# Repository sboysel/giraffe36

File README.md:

# giraffe36

A 36 key split keyboard with "long-necked" thumb clusters. Wired, powered by Raspberry Pi Picos, diodeless. Inspirations include Ferris Sweep / sweep36, draculad, samoklava, piantor.

**Status:** [v0.0.1](https://github.com/sboysel/giraffe36/releases/tag/v0.0.1) / [e54525c](https://github.com/sboysel/giraffe36/commit/e54525ce078f5a7b52e7f0cd5a91edfa0f02212c) prototypes have been tested and are functional. See [Tags](https://github.com/sboysel/giraffe36/tags).

## Goals

- simplicity
- declarative design ([ergogen](https://github.com/ergogen/ergogen) and specifically, [my fork](https://github.com/sboysel/ergogen))
- 5x3+3 wired split
- soldered MX to build plateless
- diodeless
- lowered thumb cluster comfortable to my hands
- to learn PCB design!

## Build

BOM

- 2x PCB (they are reversible, fabricated by JLCPCB)
- 2x Raspberry Pi Pico (I used [WeAct Studio Pi Picos](https://www.aliexpress.us/item/3256803521775546.html))
- 2x TRRS PJ-320A jack (4 pins)
- 36x MX switches

Be sure to use the `main` branch. Gerbers can be found in `output/pcbs/routed/`. Archives of the routed PCB and gerbers are located in `output/pcbs/routed/backups`. Firmware ([KMK](http://kmkfw.io/)) can be found in `firmware/kmk/`.

## Development 

Setup

```
git clone git@github.com:sboysel/giraffe36.git
python -m venv --system-site-packages ~/.venv/giraffe36
cd giraffe36
npm install
pip install -r requirements.txt
make
```

The `main` branch contains versions of the board that have been tested and are confirmed to be functional. The `dev` branch contains the latest progress on the next iteration.

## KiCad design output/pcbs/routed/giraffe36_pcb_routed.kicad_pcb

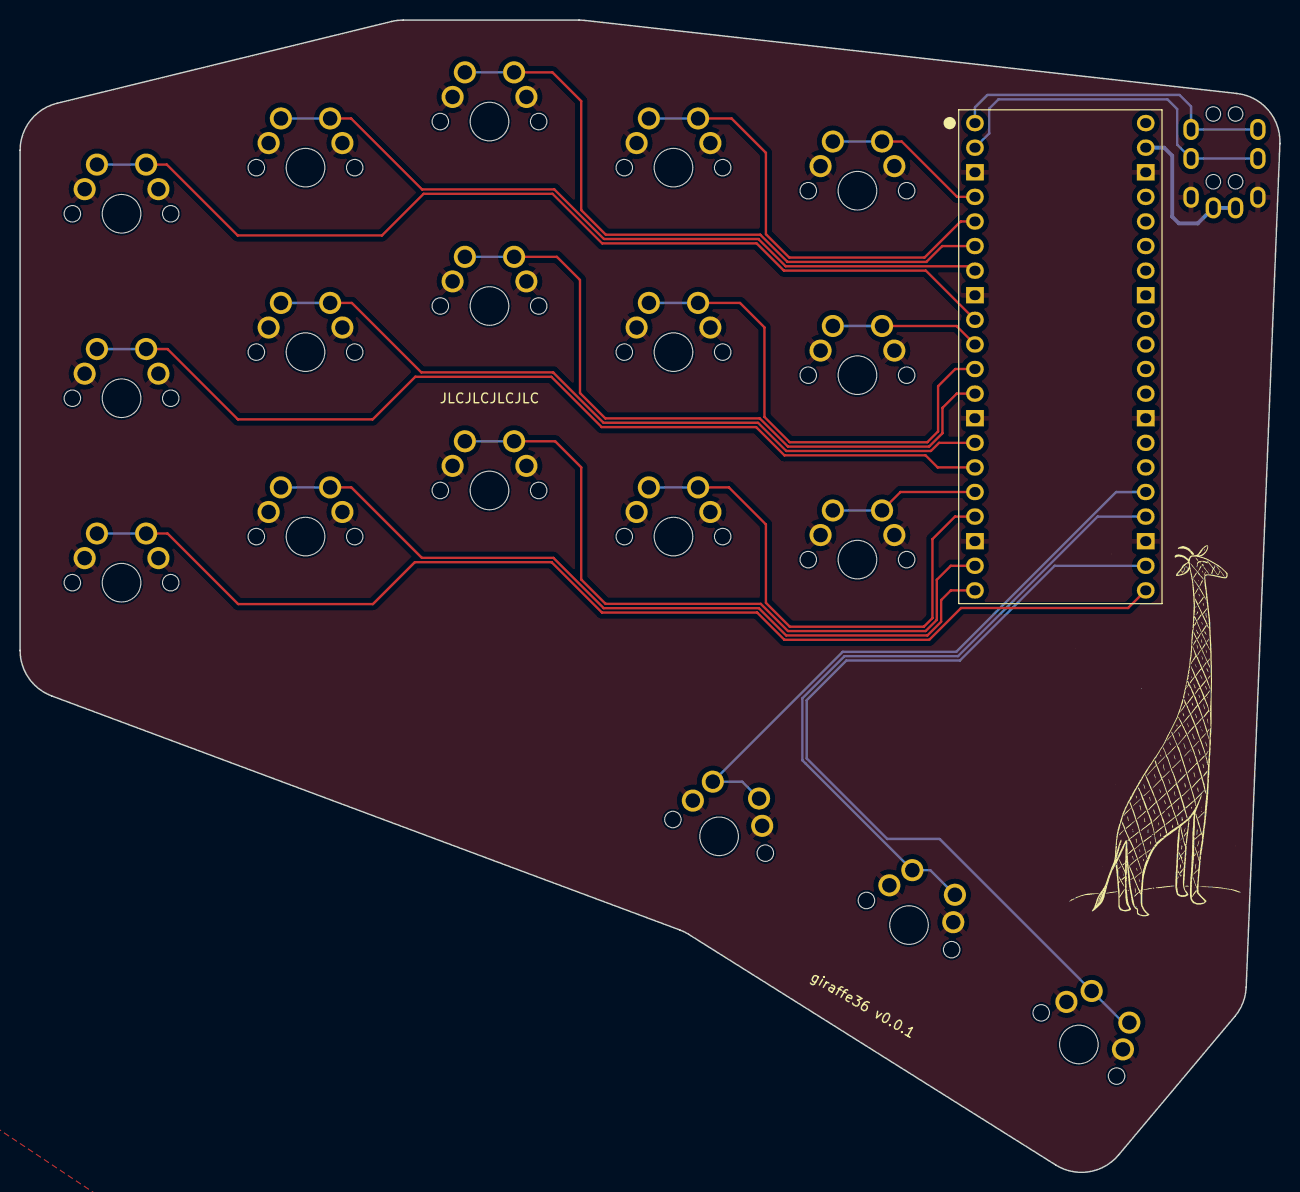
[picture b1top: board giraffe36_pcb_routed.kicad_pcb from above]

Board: 2 copper layers, 130.1 x 119.0 mm, 20 parts (0 on the bottom side), 22 nets.

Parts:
S1, S2, S3, S4, S5, S6, S7, S8, S9, S10, S11, S12, S13, S14, S15, S16, S17, S18: MX
TRRS1: TRRS-PJ-320A-dual
U0: Pico; RPi_Pico_TH_oval_face_up

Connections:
GND: S1.2, S2.2, S3.2, S4.2, S5.2, S6.2, S7.2, S8.2, S9.2, S10.2, S11.2, S12.2, S13.2, S14.2, S15.2, S16.2, S17.2, S18.2, TRRS1.2, U0.3, U0.8, U0.13, U0.18, U0.23, U0.28, U0.38
GP0: TRRS1.4, U0.1
GP1: TRRS1.3, U0.2
VSYS: TRRS1.1, U0.39
matrix_index_bottom: S10.1, U0.17
matrix_index_home: S11.1, U0.11
matrix_index_top: S12.1, U0.5
matrix_inner_bottom: S13.1, U0.16
matrix_inner_home: S14.1, U0.10
matrix_inner_top: S15.1, U0.4
matrix_middle_bottom: S7.1, U0.19
matrix_middle_home: S8.1, U0.12
matrix_middle_top: S9.1, U0.6
matrix_pinky_bottom: S1.1, U0.21
matrix_pinky_home: S2.1, U0.15
matrix_pinky_top: S3.1, U0.9
matrix_ring_bottom: S4.1, U0.20
matrix_ring_home: S5.1, U0.14
matrix_ring_top: S6.1, U0.7
thumbfan_far_home: S18.1, U0.22
thumbfan_home_home: S17.1, U0.24
thumbfan_near_home: S16.1, U0.25

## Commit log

2023-03-22 rename otter -> giraffe, more thumb splay and fillet
2023-03-22 render pcb preview in green
2023-03-24 tweak outlines and routing
2023-03-25 reduce pinky stagger
2023-03-25 remove hotswap
2023-03-26 preparing for first prototypes
2023-03-26 give TRRS are more routing breathing room
2023-03-26 prototypes are being made
2023-04-12 add firmware
2023-04-12 update Makefile
2023-04-12 adding giraffe image and footprint
2023-04-12 new layout, rp2040 zero, rj45
2023-04-12 remove extra pinout images
2023-04-12 add first build picture
2023-04-12 move routing / fabrication notes from README
2023-04-12 README: add build notes, actual build image
2023-04-12 untrack package lock
2023-04-12 add where to find gerbers
2023-04-12 clean up README
2023-04-12 update status
2023-04-12 typo
2023-04-12 Add CC-BY 4.0 license file
2023-04-12 add license badge

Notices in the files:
README.md:
CC-BY license
